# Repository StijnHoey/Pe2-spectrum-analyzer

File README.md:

# PCB's

## Informatie files:
Gebruikte tekenprogramma: Eagle 9.1.2 \
Eagle files: .sch & .brd \
Gerber files: .zip

### Informatie PCB's:
voedingequ:

Gebruikte Regelaars: LM317 & LM337 \
Emittervolger met zenerdiode: 2n3055

* Ingangsspanning:
  * 12V AC

* Uitgangsspanning:
  * -12V DC
  *   5V DC
  *  12V DC
  *  13v DC   

equlaizer:

Gebruikte OPAMP: LM072 \
Laagdoorlaatfilter en Hoogdoorlaatfilter.\
Samen opgeteld met sommeerversterker.\
Laagdoorlaatfilter voor bass.\
Hoogdoorlaatfilter voor treble. \
Versterking/verzwakking bepaald door digitale potentiometer.\
Digitale quad potentiometer: AD5263. \

Arduinoshield:\
Shield voor arduino om audio in te lezen.\
Voorzien van laagdoorlaatfilter.\
Offset regelbaar tot 3,3V.\

TDA7492:
25W stereo versterker. \
Aan/uit via shutdown pin en mute pin. \

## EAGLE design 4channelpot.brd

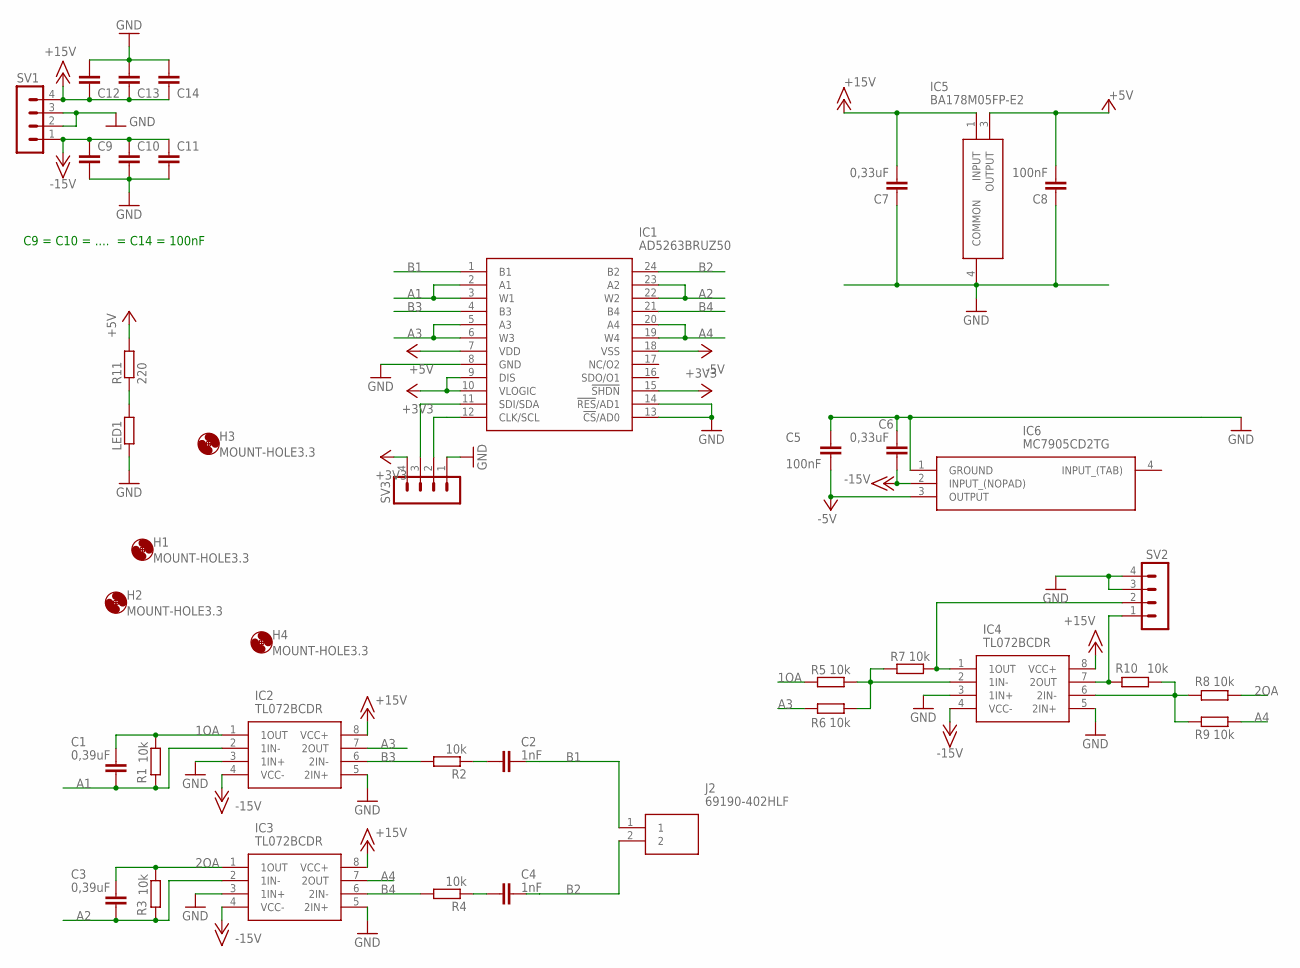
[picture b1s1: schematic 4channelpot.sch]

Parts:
C1, C3: 0,39uF; C0805
C2, C4: 1nF; C0805
C5, C8: 100nF; C0805
C6, C7: 0,33uF; C0805
C9, C10, C11, C12, C13, C14: C-EUC0805; C0805
H1, H2, H3, H4: MOUNT-HOLE3.3; 3,3
IC1: AD5263BRUZ50; SOP65P640X120-24N
IC2, IC3, IC4: TL072BCDR; SOIC127P600X175-8N
IC5: BA178M05FP-E2; BD750L5FPCE2
IC6: MC7905CD2TG; TO254P1420X457-4N
J2: 69190-402HLF; HDRV2W90P0X254_1X2_508X241X858
LED1: R-EU_R0805; R0805
R1, R2, R3, R4, R5, R6, R7, R8, R9, R10: 10k; R0805
R11: 220; R0805
SV1, SV2, SV3: MA04-1

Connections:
1OA: C1.1, IC2.1 (1OUT), R1.2, R5.2
2OA: C3.1, IC3.1 (1OUT), R3.2, R8.2
+3V3: IC1.9 (DIS), IC1.10 (VLOGIC), IC1.15 (!SHDN), SV3.4
+5V: C8.2, IC1.7 (VDD), IC5.3 (OUTPUT), R11.2
+15V: C7.2, C12.1, C13.1, C14.1, IC2.8 (VCC+), IC3.8 (VCC+), IC4.8 (VCC+), IC5.1 (INPUT), SV1.4
-5V: C5.2, IC1.18 (VSS), IC6.3 (OUTPUT)
-15V: C6.2, C9.1, C10.1, C11.1, IC2.4 (VCC-), IC3.4 (VCC-), IC4.4 (VCC-), IC6.2 (INPUT_(NOPAD)), SV1.1
A1: C1.2, IC1.2 (A1), IC1.3 (W1), IC2.2 (1IN-), R1.1
A2: C3.2, IC1.22 (W2), IC1.23 (A2), IC3.2 (1IN-), R3.1
A3: IC1.5 (A3), IC1.6 (W3), IC2.7 (2OUT), R6.2
A4: IC1.19 (W4), IC1.20 (A4), IC3.7 (2OUT), R9.2
B1: C2.1, IC1.1 (B1), J2.1
B2: C4.1, IC1.24 (B2), J2.2
B3: IC1.4 (B3), IC2.6 (2IN-), R2.2
B4: IC1.21 (B4), IC3.6 (2IN-), R4.2
GND: C5.1, C6.1, C7.1, C8.1, C9.2, C10.2, C11.2, C12.2, C13.2, C14.2, IC1.8 (GND), IC1.13 (!CS!/AD0), IC1.14 (!RES!/AD1), IC2.3 (1IN+), IC2.5 (2IN+), IC3.3 (1IN+), IC3.5 (2IN+), IC4.3 (1IN+), IC4.5 (2IN+), IC5.4 (COMMON), IC6.1 (GROUND), LED1.1, SV1.2, SV1.3, SV2.3, SV2.4, SV3.1
unnamed: IC4.2 (1IN-), R5.1, R6.1, R7.2
unnamed: IC4.1 (1OUT), R7.1, SV2.2
unnamed: LED1.2, R11.1
unnamed: C2.2, R2.1
unnamed: IC4.6 (2IN-), R8.1, R9.1, R10.2
unnamed: IC1.11 (SDI/SDA), SV3.3
unnamed: IC1.12 (CLK/SCL), SV3.2
unnamed: C4.2, R4.1
unnamed: IC4.7 (2OUT), R10.1, SV2.1

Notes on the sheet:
C9 = C10 = .... = C14 = 100nF

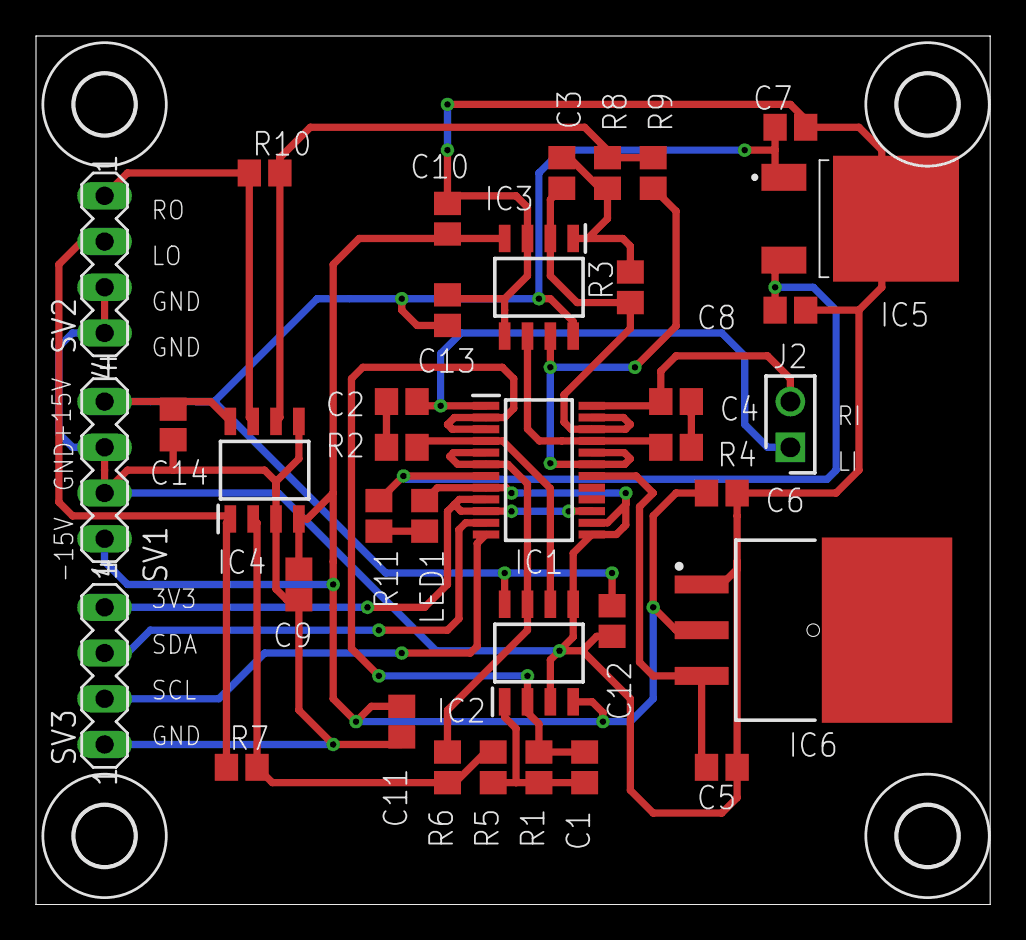
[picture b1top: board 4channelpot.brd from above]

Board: 2 copper layers, 53.0 x 48.2 mm, 40 parts (0 on the bottom side), 25 nets.

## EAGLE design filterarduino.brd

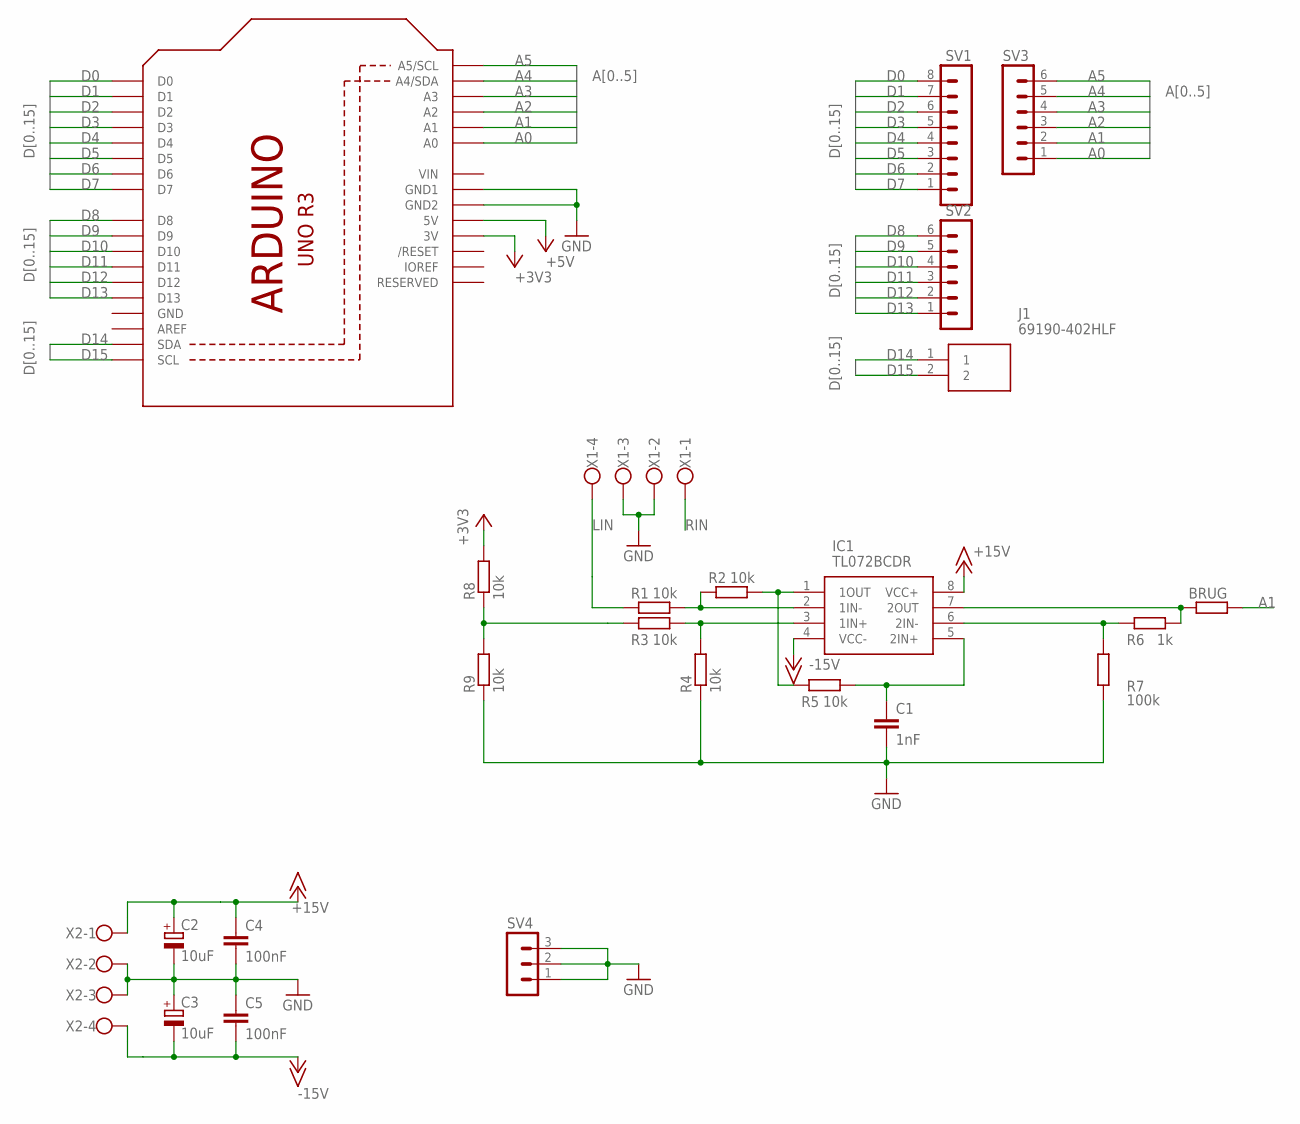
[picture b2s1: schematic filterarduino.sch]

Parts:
BRUG: 0; R0805
C1: 1nF; C0805
C2, C3: 10uF; 153CLV-0505
C4, C5: 100nF; C0805
IC1: TL072BCDR; SOIC127P600X175-8N
J1: 69190-402HLF; HDRV2W90P0X254_1X2_508X241X858
R1, R2, R3, R4, R5, R8, R9: 10k; R0805
R6: 1k; R0805
R7: 100k; R0805
SV1: MA08-1
SV2, SV3: MA06-1
SV4: MA03-1
U1: ARDUINOR3-BPLACE
X1, X2: W237-4

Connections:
+3V3: R8.2, U1.3V
+5V: U1.5V
+15V: C2.+, C4.1, IC1.8 (VCC+), X2.1
-15V: C3.-, C5.2, IC1.4 (VCC-), X2.4
A0: SV3.1, U1.A0
A1: BRUG.2, SV3.2, U1.A1
A2: SV3.3, U1.A2
A3: SV3.4, U1.A3
A4: SV3.5, U1.A4 (A4/SDA)
A5: SV3.6, U1.A5 (A5/SCL)
D0: SV1.8, U1.D0
D1: SV1.7, U1.D1
D2: SV1.6, U1.D2
D3: SV1.5, U1.D3
D4: SV1.4, U1.D4
D5: SV1.3, U1.D5
D6: SV1.2, U1.D6
D7: SV1.1, U1.D7
D8: SV2.6, U1.D8
D9: SV2.5, U1.D9
D10: SV2.4, U1.D10
D11: SV2.3, U1.D11
D12: SV2.2, U1.D12
D13: SV2.1, U1.D13
D14: J1.1, U1.SDA
D15: J1.2, U1.SCL
GND: C1.2, C2.-, C3.+, C4.2, C5.1, R4.1, R7.1, R9.1, SV4.1, SV4.2, SV4.3, U1.GND, U1.GND1, U1.GND2, X1.2, X1.3, X2.2, X2.3
LIN: R1.1, X1.4
unnamed: IC1.2 (1IN-), R1.2, R2.1
unnamed: IC1.3 (1IN+), R3.2, R4.2
unnamed: IC1.1 (1OUT), R2.2, R5.2
unnamed: C1.1, IC1.5 (2IN+), R5.1
unnamed: BRUG.1, IC1.7 (2OUT), R6.2
unnamed: IC1.6 (2IN-), R6.1, R7.2
unnamed: R3.1, R8.1, R9.2
RIN: X1.1
VIN: U1.VIN

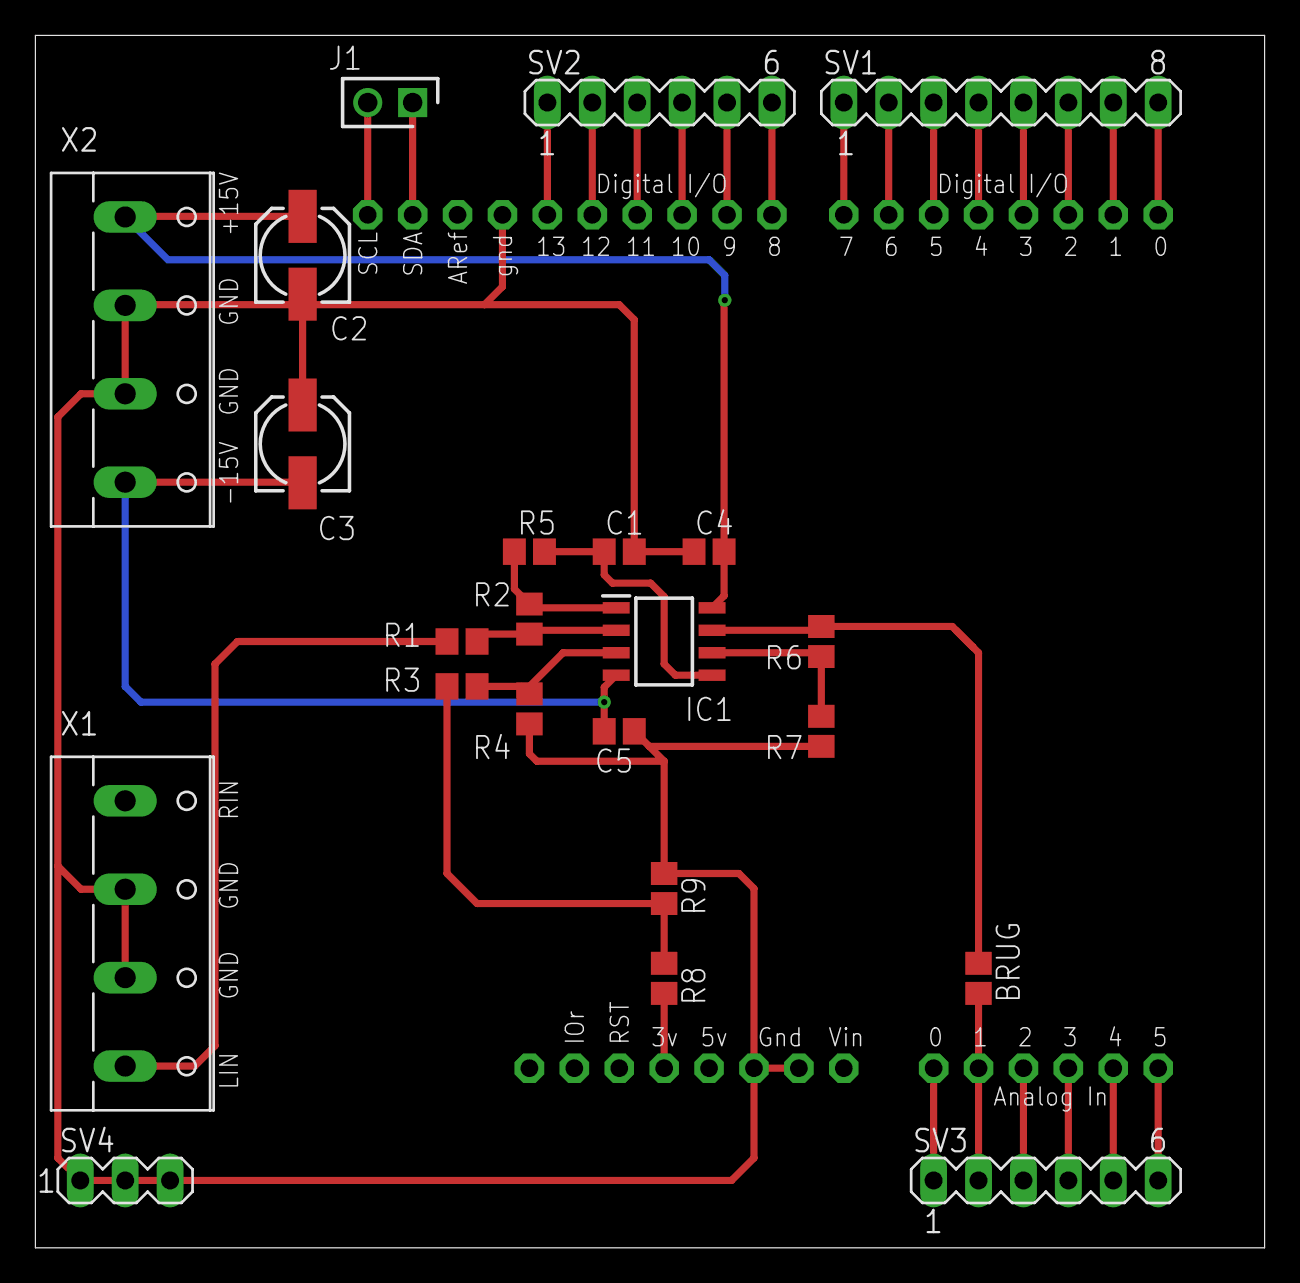
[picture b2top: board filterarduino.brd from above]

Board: 2 copper layers, 69.5 x 68.6 mm, 24 parts (0 on the bottom side), 34 nets.

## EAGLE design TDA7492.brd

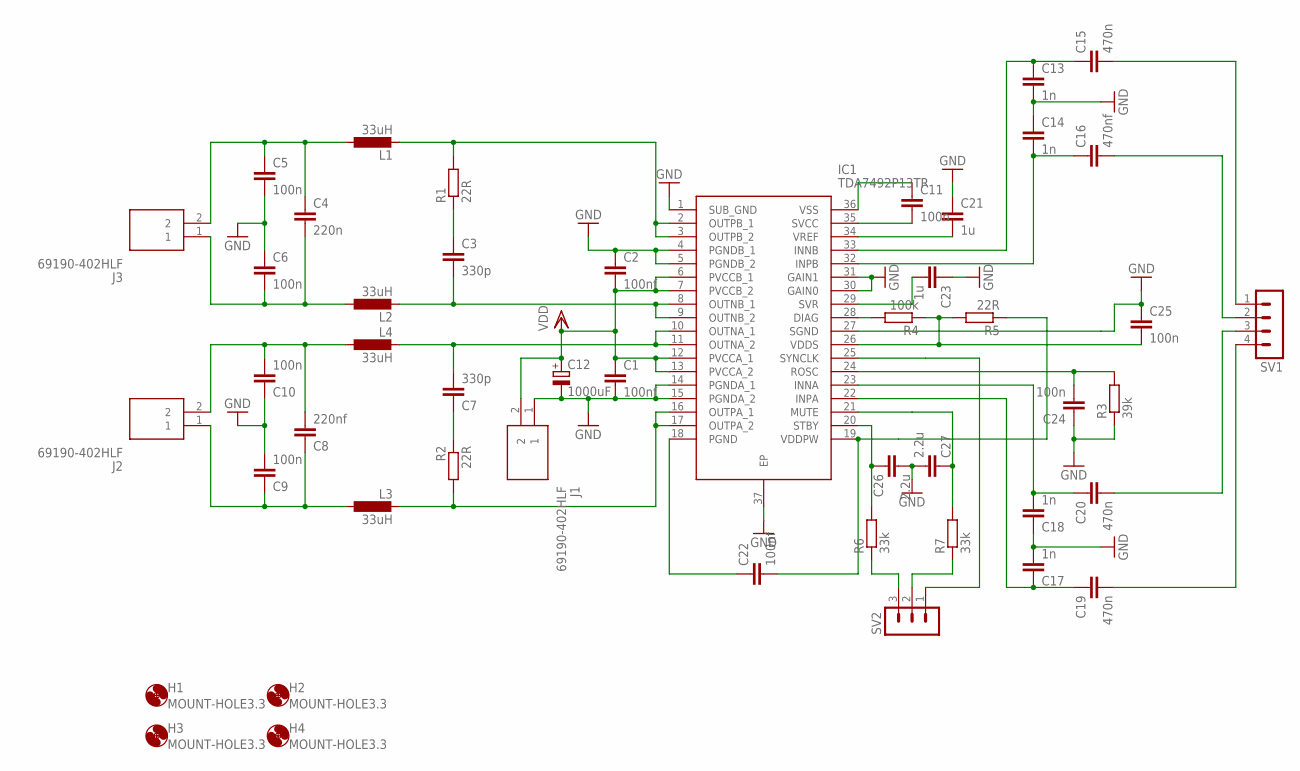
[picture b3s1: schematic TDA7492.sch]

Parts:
C1, C2, C22: 100nf; C0805
C3, C7: 330p; C0805
C4: 220n; C0805
C5, C6, C9, C10, C11, C24, C25: 100n; C0805
C8: 220nf; C0805
C12: 1000uF; E7,5-16
C13, C14, C17, C18: 1n; C0805
C15, C19, C20: 470n; C0805
C16: 470nf; C0805
C21, C23: 1u; C0805
C26, C27: 2.2u; C0805
H1, H2, H3, H4: MOUNT-HOLE3.3; 3,3
IC1: TDA7492P13TR; SOP50P1030X245-37N
J1, J2, J3: 69190-402HLF; HDRV2W90P0X254_1X2_508X241X858
L1, L2, L3, L4: 33uH; POWER-CHOKE_WE-TPC
R1, R2, R5: 22R; R0805
R3: 39k; R0805
R4: 100k; R0805
R6, R7: 33k; R0805
SV1: MA04-1
SV2: MA03-1

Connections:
GND: C1.2, C2.1, C5.2, C6.1, C9.2, C10.1, C12.-, C13.2, C14.1, C17.2, C18.1, C21.1, C23.1, C24.1, C25.1, C26.2, C27.2, IC1.1 (SUB_GND), IC1.4 (PGNDB_1), IC1.5 (PGNDB_2), IC1.14 (PGNDA_1), IC1.15 (PGNDA_2), IC1.27 (SGND), IC1.30 (GAIN0), IC1.31 (GAIN1), IC1.37 (EP), J1.1, R3.1
unnamed: C4.2, C6.2, J3.1, L2.1
unnamed: C4.1, C5.1, J3.2, L1.1
unnamed: IC1.2 (OUTPB_1), IC1.3 (OUTPB_2), L1.2, R1.2
unnamed: IC1.16 (OUTPA_1), IC1.17 (OUTPA_2), L3.2, R2.2
unnamed: C3.2, IC1.8 (OUTNB_1), IC1.9 (OUTNB_2), L2.2
unnamed: C11.2, IC1.35 (SVCC)
unnamed: C24.2, IC1.24 (ROSC), R3.2
unnamed: C3.1, R1.1
unnamed: C23.2, IC1.29 (SVR)
unnamed: C14.2, C16.1, IC1.32 (INPB)
unnamed: C7.2, IC1.10 (OUTNA_1), IC1.11 (OUTNA_2), L4.2
unnamed: C8.2, C10.2, J2.2, L4.1
unnamed: C8.1, C9.1, J2.1, L3.1
unnamed: C7.1, R2.1
unnamed: C11.1, IC1.36 (VSS)
unnamed: C13.1, C15.1, IC1.33 (INNB)
unnamed: C22.1, IC1.18 (PGND)
unnamed: C17.1, C19.1, IC1.22 (INPA)
unnamed: C21.2, IC1.34 (VREF)
unnamed: C18.2, C20.1, IC1.23 (INNA)
unnamed: C22.2, IC1.19 (VDDPW), R5.1
unnamed: C15.2, SV1.1
unnamed: C16.2, SV1.2
unnamed: C20.2, SV1.3
unnamed: C19.2, SV1.4
unnamed: C27.1, IC1.21 (MUTE), R7.2
unnamed: IC1.28 (DIAG), R4.2
unnamed: C25.2, IC1.26 (VDDS), R4.1, R5.2
unnamed: IC1.25 (SYNCLK), SV2.1
unnamed: C26.1, IC1.20 (STBY), R6.2
unnamed: R6.1, SV2.3
unnamed: R7.1, SV2.2
VDD: C1.1, C2.2, C12.+, IC1.6 (PVCCB_1), IC1.7 (PVCCB_2), IC1.12 (PVCCA_1), IC1.13 (PVCCA_2), J1.2

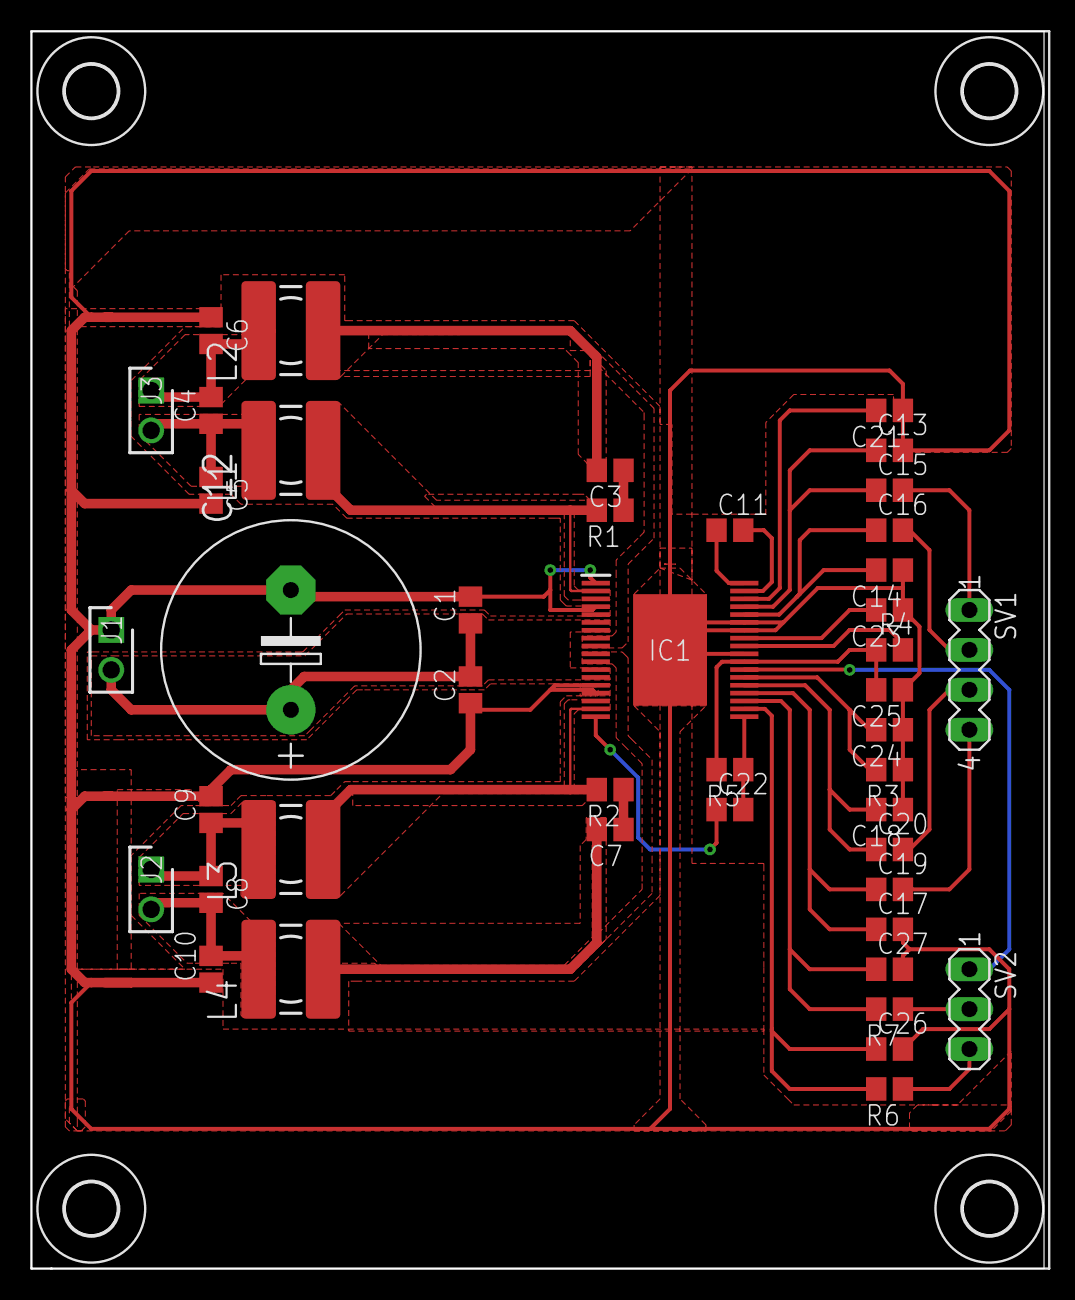
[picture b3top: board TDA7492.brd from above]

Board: 2 copper layers, 64.4 x 78.7 mm, 48 parts (0 on the bottom side), 34 nets.

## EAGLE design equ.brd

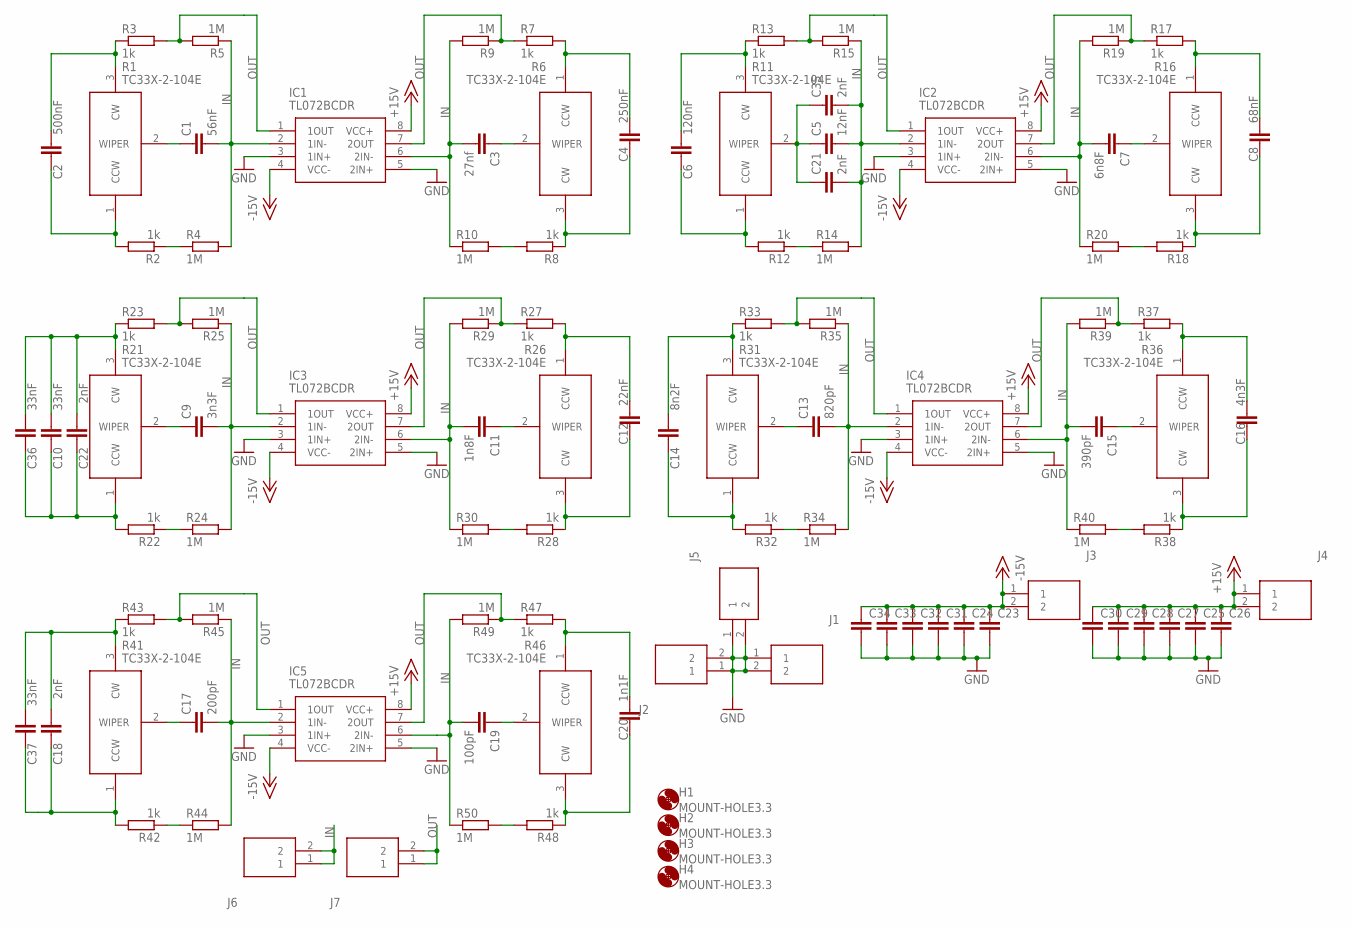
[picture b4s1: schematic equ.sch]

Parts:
C1: 56nF; C0805
C2: 500nF; C0805
C3: 27nf; C0805
C4: 250nF; C0805
C5: 12nF; C0805
C6: 120nF; C0805
C7: 6n8F; C0805
C8: 68nF; C0805
C9: 3n3F; C0805
C10, C36, C37: 33nF; C0805
C11: 1n8F; C0805
C12: 22nF; C0805
C13: 820pF; C0805
C14: 8n2F; C0805
C15: 390pF; C0805
C16: 4n3F; C0805
C17: 200pF; C0805
C18, C21, C22, C35: 2nF; C0805
C19: 100pF; C0805
C20: 1n1F; C0805
C23, C24, C25, C26, C27, C28, C29, C30, C31, C32, C33, C34: C-EUC0805; C0805
H1, H2, H3, H4: MOUNT-HOLE3.3; 3,3
IC1, IC2, IC3, IC4, IC5: TL072BCDR; SOIC127P600X175-8N
J1, J2, J3, J4, J5, J6, J7: 69190-402HLF; HDRV2W90P0X254_1X2_508X241X858
R1, R6, R11, R16, R21, R26, R31, R36, R41, R46: TC33X-2-104E; TC33X-2
R2, R3, R7, R8, R12, R13, R17, R18, R22, R23, R27, R28, R32, R33, R37, R38, R42, R43, R47, R48: 1k; R0805
R4, R5, R9, R10, R14, R15, R19, R20, R24, R25, R29, R30, R34, R35, R39, R40, R44, R45, R49, R50: 1M; R0805

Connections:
+15V: C25.1, C26.1, C27.1, C28.1, C29.1, C30.1, IC1.8 (VCC+), IC2.8 (VCC+), IC3.8 (VCC+), IC4.8 (VCC+), IC5.8 (VCC+), J4.1, J4.2
-15V: C23.1, C24.1, C31.1, C32.1, C33.1, C34.1, IC1.4 (VCC-), IC2.4 (VCC-), IC3.4 (VCC-), IC4.4 (VCC-), IC5.4 (VCC-), J3.1, J3.2
GND: C23.2, C24.2, C25.2, C26.2, C27.2, C28.2, C29.2, C30.2, C31.2, C32.2, C33.2, C34.2, IC1.3 (1IN+), IC1.5 (2IN+), IC2.3 (1IN+), IC2.5 (2IN+), IC3.3 (1IN+), IC3.5 (2IN+), IC4.3 (1IN+), IC4.5 (2IN+), IC5.3 (1IN+), IC5.5 (2IN+), J1.1, J1.2, J2.1, J2.2, J5.1, J5.2
IN: C1.2, C3.2, C5.2, C7.2, C9.2, C11.2, C13.2, C15.2, C17.2, C19.2, C21.2, C35.2, IC1.2 (1IN-), IC1.6 (2IN-), IC2.2 (1IN-), IC2.6 (2IN-), IC3.2 (1IN-), IC3.6 (2IN-), IC4.2 (1IN-), IC4.6 (2IN-), IC5.2 (1IN-), IC5.6 (2IN-), J6.1, J6.2, R4.2, R5.1, R9.2, R10.1, R14.2, R15.1, R19.2, R20.1, R24.2, R25.1, R29.2, R30.1, R34.2, R35.1, R39.2, R40.1, R44.2, R45.1, R49.2, R50.1
unnamed: C2.1, R1.1 (CCW), R2.2
unnamed: C2.2, R1.3 (CW), R3.1
unnamed: C1.1, R1.2 (WIPER)
unnamed: R2.1, R4.1
unnamed: C6.1, R11.1 (CCW), R12.2
unnamed: C4.1, R6.1 (CCW), R7.2
unnamed: C4.2, R6.3 (CW), R8.1
unnamed: C3.1, R6.2 (WIPER)
unnamed: C6.2, R11.3 (CW), R13.1
unnamed: R8.2, R10.2
unnamed: C5.1, C21.1, C35.1, R11.2 (WIPER)
unnamed: R12.1, R14.1
unnamed: C8.1, R16.1 (CCW), R17.2
unnamed: C8.2, R16.3 (CW), R18.1
unnamed: C7.1, R16.2 (WIPER)
unnamed: R18.2, R20.2
unnamed: C18.1, C37.1, R41.1 (CCW), R42.2
unnamed: C18.2, C37.2, R41.3 (CW), R43.1
unnamed: C9.1, R21.2 (WIPER)
unnamed: R22.1, R24.1
unnamed: C12.1, R26.1 (CCW), R27.2
unnamed: C12.2, R26.3 (CW), R28.1
unnamed: C11.1, R26.2 (WIPER)
unnamed: R28.2, R30.2
unnamed: C14.1, R31.1 (CCW), R32.2
unnamed: C14.2, R31.3 (CW), R33.1
unnamed: C13.1, R31.2 (WIPER)
unnamed: R32.1, R34.1
unnamed: C16.1, R36.1 (CCW), R37.2
unnamed: C16.2, R36.3 (CW), R38.1
unnamed: C15.1, R36.2 (WIPER)
unnamed: R38.2, R40.2
unnamed: C17.1, R41.2 (WIPER)
unnamed: R42.1, R44.1
unnamed: C20.1, R46.1 (CCW), R47.2
unnamed: C20.2, R46.3 (CW), R48.1
unnamed: C19.1, R46.2 (WIPER)
unnamed: R48.2, R50.2
unnamed: C10.1, C22.2, C36.1, R21.1 (CCW), R22.2
unnamed: C10.2, C22.1, C36.2, R21.3 (CW), R23.1
OUT: IC1.1 (1OUT), IC1.7 (2OUT), IC2.1 (1OUT), IC2.7 (2OUT), IC3.1 (1OUT), IC3.7 (2OUT), IC4.1 (1OUT), IC4.7 (2OUT), IC5.1 (1OUT), IC5.7 (2OUT), J7.1, J7.2, R3.2, R5.2, R7.1, R9.1, R13.2, R15.2, R17.1, R19.1, R23.2, R25.2, R27.1, R29.1, R33.2, R35.2, R37.1, R39.1, R43.2, R45.2, R47.1, R49.1

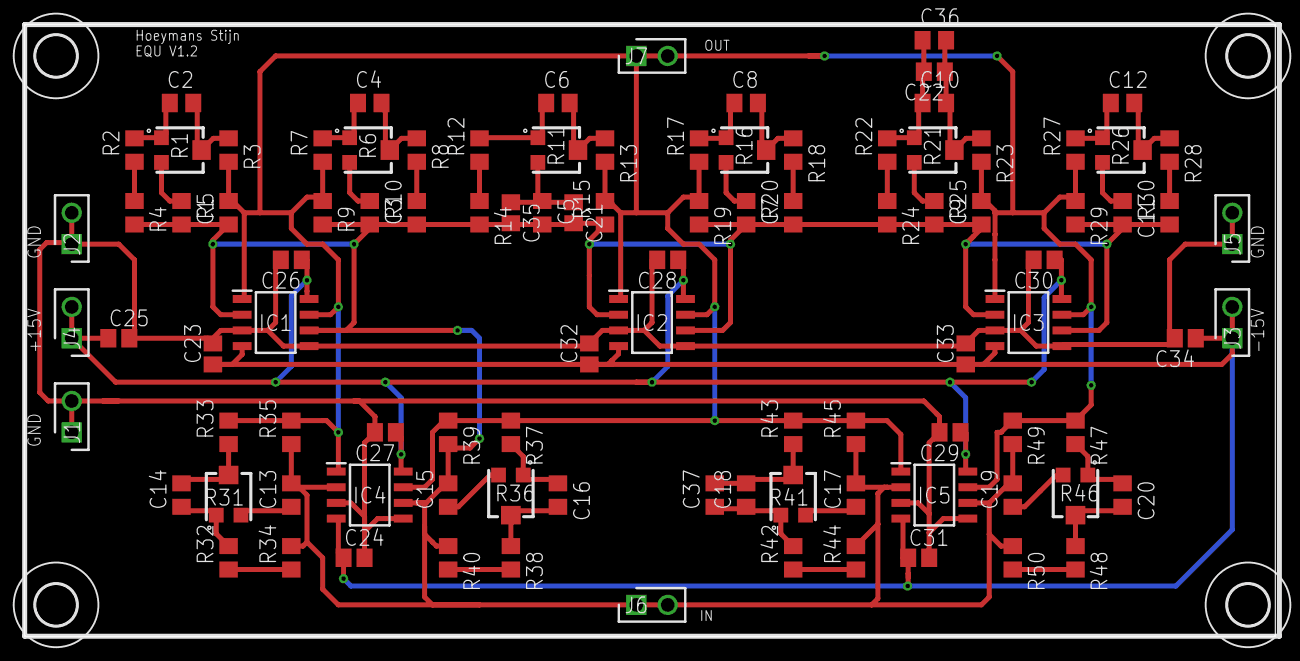
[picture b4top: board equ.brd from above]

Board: 2 copper layers, 101.3 x 49.5 mm, 103 parts (0 on the bottom side), 45 nets.

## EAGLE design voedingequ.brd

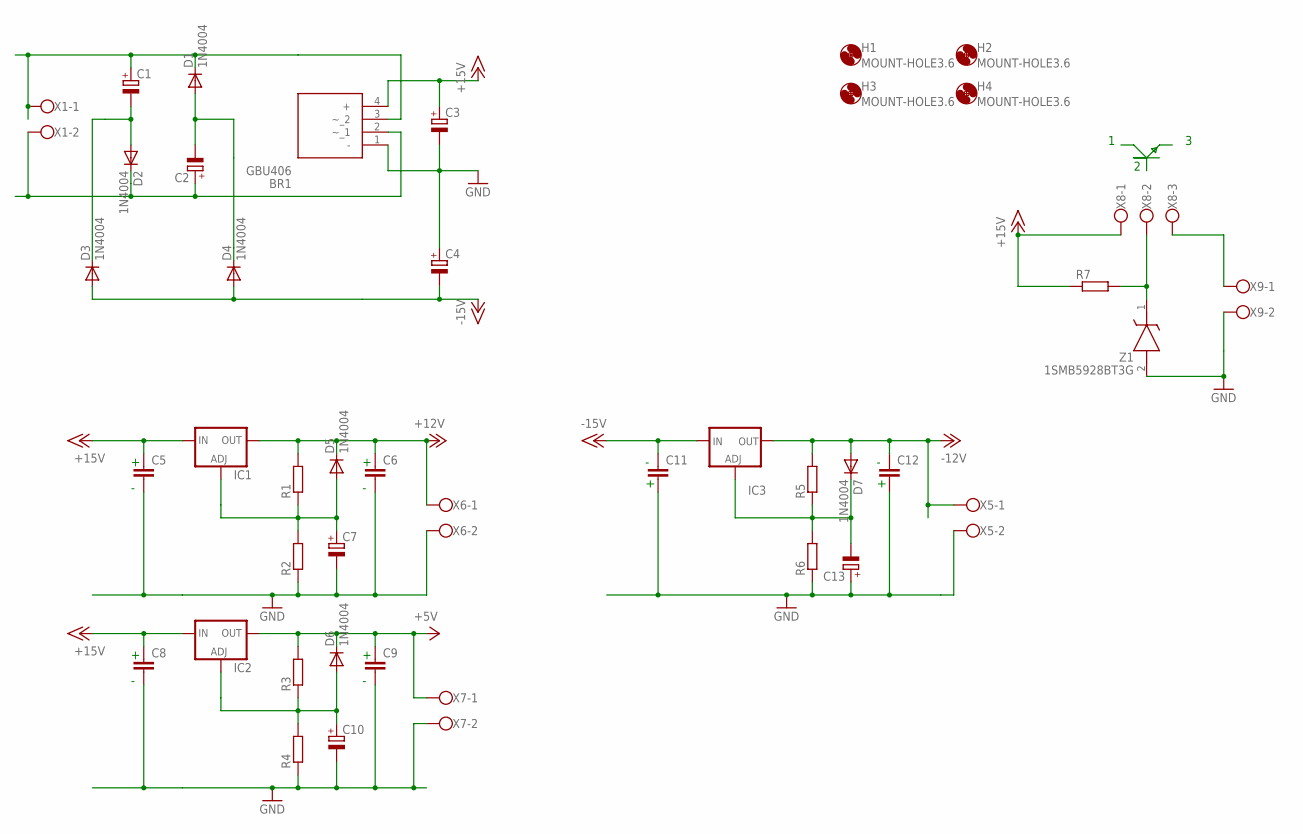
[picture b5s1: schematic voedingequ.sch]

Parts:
BR1: GBU406; TO508P356X2205X2135-4P
C1, C2, C3, C4: CPOL-EUE5-10.5; E5-10,5
C5, C6, C8, C9, C11, C12: C-EUC0805; C0805
C7, C10, C13: CPOL-EU153CLV-0505; 153CLV-0505
D1, D2, D3, D4, D5, D6, D7: 1N4004; DO41-10
H1, H2, H3, H4: MOUNT-HOLE3.6; 3,6
IC1, IC2: LM317TS; 317TS
IC3: LM337TS; 337TS
R1, R2, R3, R4, R5, R6: R-EU_R0805; R0805
R7: R-EU_R2512; R2512
X1, X5, X6, X7, X9: W237-102
X8: W237-103
Z1: 1SMB5928BT3G; DIOM5436X247N

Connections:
+5V: C9.1, D6.C, IC2.2 (OUT), R3.2, X7.1
+12V: C6.1, D5.C, IC1.2 (OUT), R1.2, X6.1
+15V: BR1.4 (+), C3.+, C5.1, C8.1, IC1.3 (IN), IC2.3 (IN), R7.1, X8.1
-12V: C12.1, D7.A, IC3.3 (OUT), R5.2, X5.1
-15V: C4.-, C11.1, D3.A, D4.A, IC3.2 (IN)
GND: BR1.1 (-), C3.-, C4.+, C5.2, C6.2, C7.-, C8.2, C9.2, C10.-, C11.2, C12.2, C13.+, R2.1, R4.1, R6.1, X5.2, X6.2, X7.2, X9.2, Z1.2 (A)
unnamed: C1.-, D2.A, D3.C
unnamed: C2.-, D1.A, D4.C
unnamed: BR1.3 (~_2), C1.+, D1.C, X1.1
unnamed: BR1.2 (~_1), C2.+, D2.C, X1.2
unnamed: C13.-, D7.C, IC3.1 (ADJ), R5.1, R6.2
unnamed: C7.+, D5.A, IC1.1 (ADJ), R1.1, R2.2
unnamed: X8.3, X9.1
unnamed: R7.2, X8.2, Z1.1 (K)
unnamed: C10.+, D6.A, IC2.1 (ADJ), R3.1, R4.2

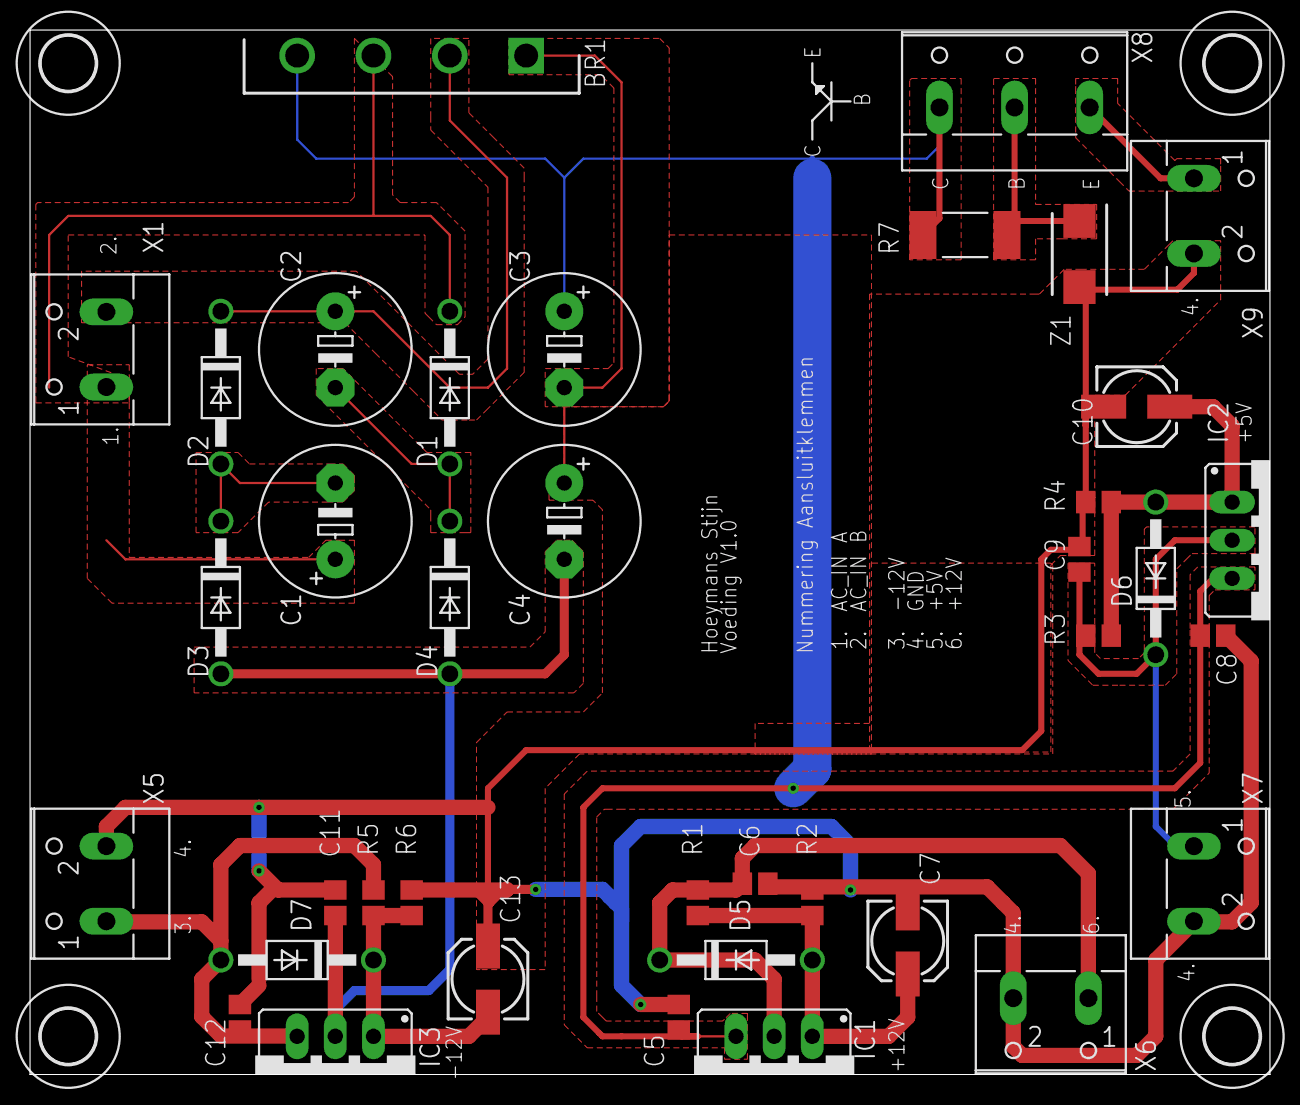
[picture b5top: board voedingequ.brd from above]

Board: 2 copper layers, 82.5 x 69.5 mm, 42 parts (0 on the bottom side), 15 nets.
